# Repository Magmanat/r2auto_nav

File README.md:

# r2auto_nav
ROS2 auto_nav code for EG2310, sem2 AY21/22

Welcome to group4's repo for EG2310, and this is all our code for our Beta Gasoline robot.

Please follow our step by step guide to start up your system. We are assuming that you are using the exact same hardware as us, such as our launcher and loading system, and our electrical connections.

## Preparation
#### Do the following things to setup your laptop and turtlebot

 1. Follow the instructions here to setup your laptop and turtlebot https://emanual.robotis.com/docs/en/platform/turtlebot3/quick-start/
 2. Follow this for instructions on setting up i2c communication on the turtlebot's raspberry pi https://ask.wingware.com/question/3/i2c-problem-with-remote-raspberry-pi/
 3. Follow this for instructions on setting up gpiozero and pigpio pin factory (so that the servo used will not spasm) https://gpiozero.readthedocs.io/en/stable/remote_gpio.html
  4. Check our our /Hardware folder for the schematics of the pcbs that we use to replicate our robot system. **IMPORTANT! FOR OUR 12V SUPPLY AS STATED IN OUR RPI HAT PCB, WE USED 5V INSTEAD DUE TO 12V SPINNING OUR MOTORS TOO FAST AND CAUSING OSCILLATIONS ON OUR ROBOT**

## File allocation and building of workspaces
clone our repository into your Home directory.

    git clone https://github.com/Magmanat/r2auto_nav.git
 Then shift the entire folder hardware_bringup into your turtlebot3_ws using scp, then build the workspace, for example

    scp -r path_to_r2auto_nav/turtlebot3_ws/src/hardware_bringup ubuntu@(ip-address-of-pi):~/turtlebot3/src
    ssh ubuntu@(ip-address-of-pi)
    cd turtlebot3_ws
    colcon build
  
  cd into colcon_ws and colcon build the workspace to setup the ros package on your laptop

    cd path_to_r2auto_nav/colcon_ws
    colcon build
  Your should be done setting up after this, now its time to have fun with our package
  
  ## System check
Firstly, we will use the factory_test package to ensure that everything is running properly, we will ssh into the turtlebot and startup all the hardware publishers and subscribers.

#### For your Turtlebot
##### In one terminal
    ssh ubuntu@(ip-address-of-pi)
    roslaunch turtlebot3_bringup turtlebot3_robot.launch
##### In another terminal
    ssh ubuntu@(ip-address-of-pi)
    ros2 launch hardware_bringup hardware.launch.py
  
Finally, we will run the script in your laptop to check that the whole system is working
#### For your Laptop
##### In one terminal
    ros2 run auto_nav factory_test

Follow the instructions printed on your terminal, and if everything works out fine, it means the system is ready to go.

## Running auto_nav in a maze
Now we will get to try the robot in an actual maze, and see it complete its mission, prepare two terminals for your Turtlebot and prepare 3 terminals for your Laptop.
Similarly, we will start all the hardware in the Turtlebot first.
#### For your Turtlebot
##### In one terminal
    ssh ubuntu@(ip-address-of-pi)
    roslaunch turtlebot3_bringup turtlebot3_robot.launch
##### In another terminal
    ssh ubuntu@(ip-address-of-pi)
    ros2 launch hardware_bringup hardware.launch.py
  
Finally, we will run the commands to start the auto navigation
#### For your Laptop
##### First terminal
    ros2 launch turtlebot3_cartographer cartographer.launch.py
Ensure that you see rviz open up, laserscan and map data will be able to be seen on the rviz window.
##### Second terminal
    ros2 run auto_nav map2base
Ensure that the transforms are properly being published by observing the terminal for any error messages that print.
##### Third terminal
    ros2 run auto_nav wall_follow
Finally, after running this command, the robot should move around and perform its mission autonomously, moving around the maze and stopping at an nfc loading bay, which it will then stop and wait to be loaded and button to be pressed to continue with its mission. After moving one entire round around the maze, and also being loaded, it will then search for a thermal target, which when found, the turtlebot would start centering towards the target and finally when the target is approximately 15 cm away from the turtlebot, it would stop and start the firing sequence.

## Parameters that affect operation of the robot
From lines 35 to 57 of /colcon_ws/src/auto_nav/auto_nav/r2_wall_follow.py

The explanation of all the parameters are as commented below. These are the values which we found work the best for us in our use case. Please change these values if you require a different behavior of the robot.

    #variables affecting targeting
    TARGETspeedchange = 0.05 #forward speed for targeting
    TARGETrotatechange = 0.1 #rotation speed for targeting
    TARGET_hotthreshhold = 31 #target temperature
    TARGETshoot_distance = 0.45 #distance from center of lidar to front before shooting
    TARGET_front_angle = 3 #angle of front to measure distance
    TARGET_moveres = 0.2 #time for sleep when moving
    TARGET_target_not_detected_threshhold = 2 #How long in seconds before target considered as not detected

    # variables affecting navigation
    fastspeedchange = 0.2 #speed when bot moving fast linear speed
    slowspeedchange = 0.12 #speed when bot moving slow linear speed
    
    turning_speed_wf_fast = 1.1 #fast turning speed for bot
    turning_speed_wf_medium = 0.75 #medium turning speed for bot
    turning_speed_wf_slow = 0.5 #slow turning speed for bot
    
    front_d = 0.45 #threshhold front distance that robot should not enter
    side_d = 0.45 #threshold side distance that robot should not enter
    
    target_count_threshhold = 5 # (how long you want hot_target to be spotted before activating firing) / hot_timer_delay = target_count_threshhold
    hot_timer_delay = 0.1 # in seconds

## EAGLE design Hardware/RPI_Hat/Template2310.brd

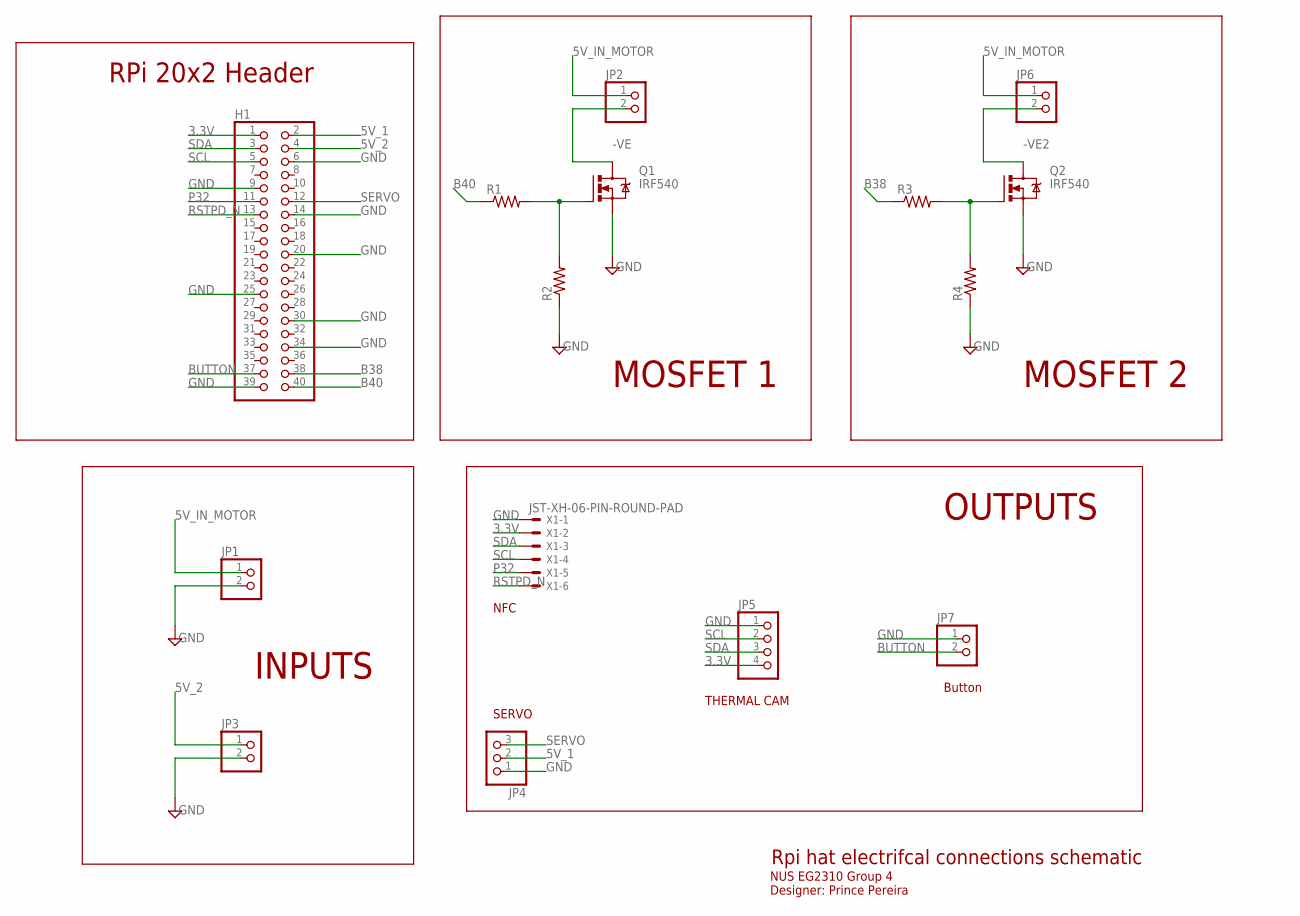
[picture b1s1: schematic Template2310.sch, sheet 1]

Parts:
H1: PINHD-2X20; 2X20
JP1, JP2, JP3, JP6: PINHD-1X2; 1X02
JP4: PINHD-1X3/90; 1X03/90
JP5: PINHD-1X4/90; 1X04/90
JP7: PINHD-1X2/90; 1X02/90
Q1, Q2: IRF540; TO220BV
R1, R2, R3, R4: R-US_0204/7; 0204/7
X1: JST-XH-06-PIN-ROUND-PAD; JST-XH-06-PACKAGE-ROUND-PAD

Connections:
3.3V: H1.1, JP5.4, X1.2
5V_1: H1.2, JP4.2
5V_2: H1.4, JP3.1
5V_IN_MOTOR: JP1.1, JP2.1, JP6.1
-VE: JP2.2, Q1.D
-VE2: JP6.2, Q2.D
B38: H1.38, R3.1
B40: H1.40, R1.1
BUTTON: H1.37, JP7.2
GND: H1.6, H1.9, H1.14, H1.20, H1.25, H1.30, H1.34, H1.39, JP1.2, JP3.2, JP4.1, JP5.1, JP7.1, Q1.S, Q2.S, R2.1, R4.1, X1.1
JUNCTION: Q1.G, R1.2, R2.2
JUNCTION1: Q2.G, R3.2, R4.2
P32: H1.11, X1.5
RSTPD_N: H1.13, X1.6
SCL: H1.5, JP5.2, X1.4
SDA: H1.3, JP5.3, X1.3
SERVO: H1.12, JP4.3

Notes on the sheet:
Rpi hat electrifcal connections schematic
NUS EG2310 Group 4 Designer: Prince Pereira
RPi 20x2 Header
MOSFET 1
INPUTS
OUTPUTS
NFC
SERVO
THERMAL CAM
MOSFET 2
Button

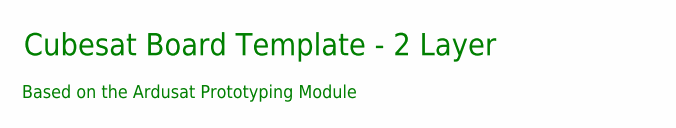
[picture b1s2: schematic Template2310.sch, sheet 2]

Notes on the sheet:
Cubesat Board Template - 2 Layer
Based on the Ardusat Prototyping Module

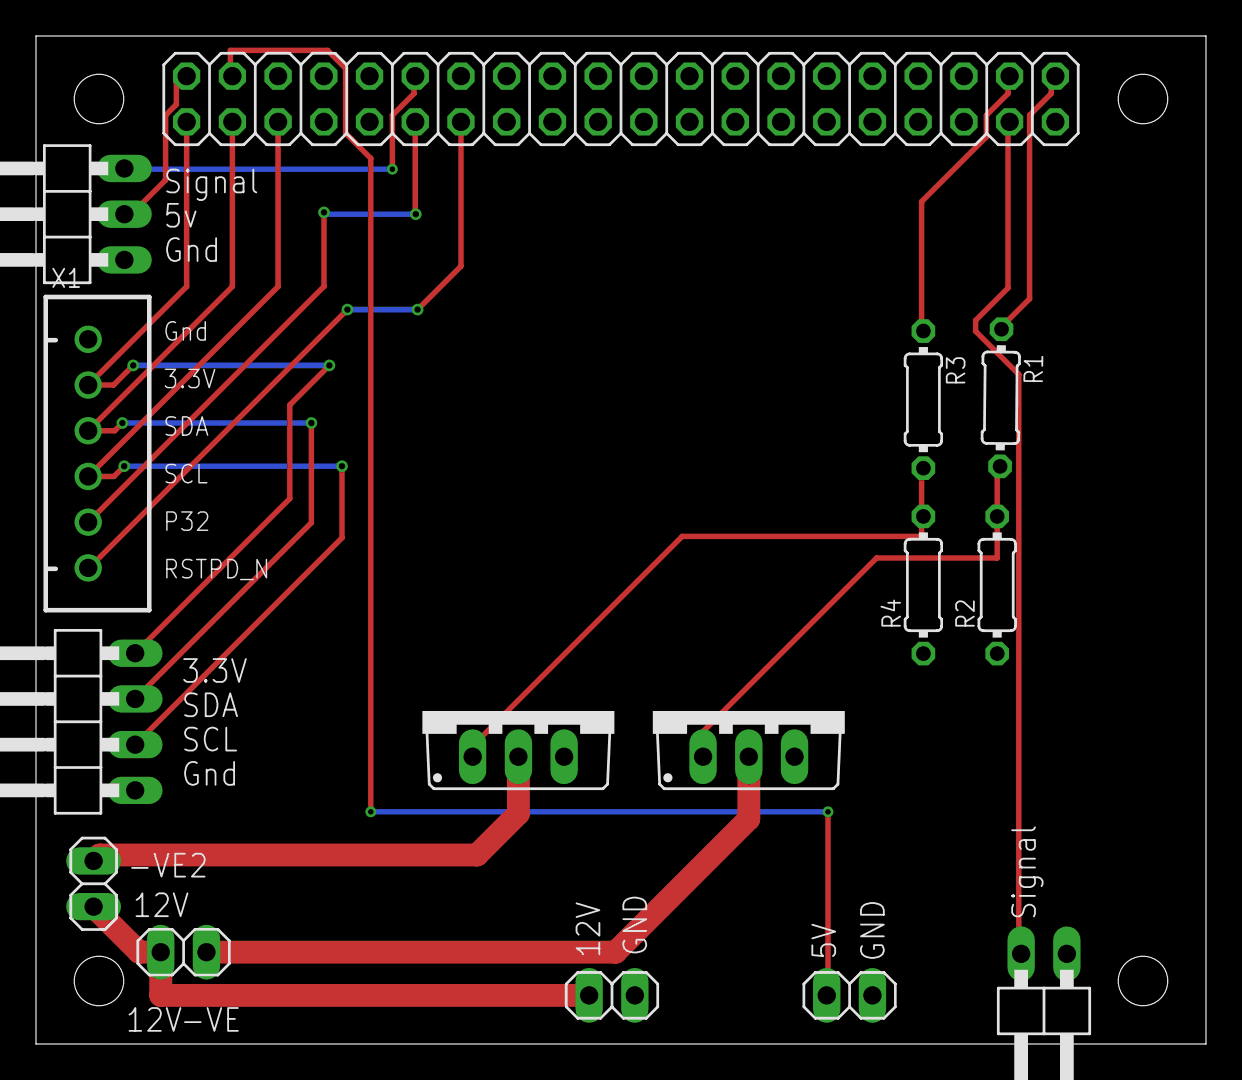
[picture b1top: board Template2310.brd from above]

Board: 2 copper layers, 65.0 x 56.0 mm, 15 parts (0 on the bottom side), 17 nets.

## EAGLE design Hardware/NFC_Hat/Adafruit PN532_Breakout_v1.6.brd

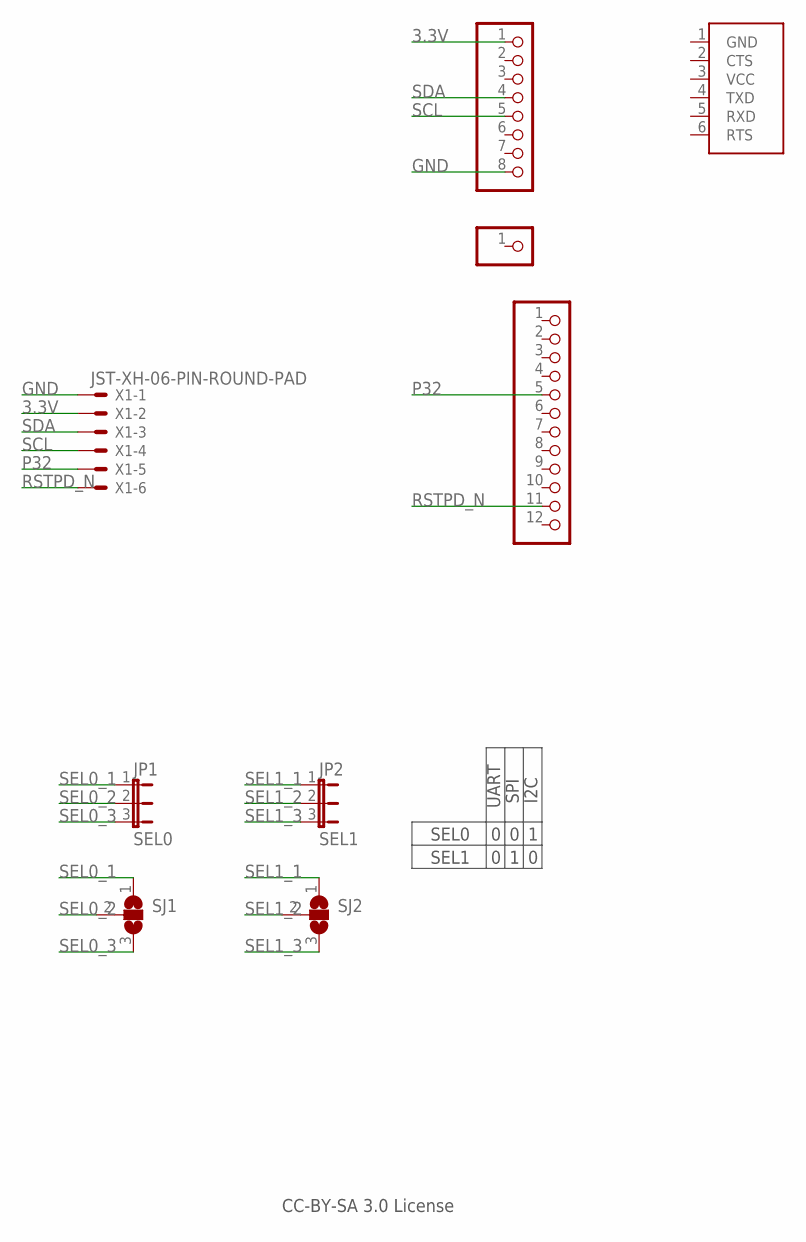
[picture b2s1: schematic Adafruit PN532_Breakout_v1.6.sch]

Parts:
CN1: FTDI; 1X06_ROUND
JP1: SEL0; JUMPER3
JP2: SEL1; JUMPER3
JP3: HEADER-1X12; 1X12_ROUND
JP4: HEADER-1X8ROUND; 1X08_ROUND
JP5: HEADER-1X1ROUND; 1X01_ROUND
SJ1, SJ2: SJ2W; SJ_2
X1: JST-XH-06-PIN-ROUND-PAD; JST-XH-06-PACKAGE-ROUND-PAD

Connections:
3.3V: JP4.1, X1.2
GND: JP4.8, X1.1
P32: JP3.5, X1.5
RSTPD_N: JP3.11, X1.6
SCL: JP4.5, X1.4
SDA: JP4.4, X1.3
SEL0_1: JP1.1, SJ1.1
SEL0_2: JP1.2, SJ1.2
SEL0_3: JP1.3, SJ1.3
SEL1_1: JP2.1, SJ2.1
SEL1_2: JP2.2, SJ2.2
SEL1_3: JP2.3, SJ2.3

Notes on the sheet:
SEL0
SEL1
UART
SPI
I2C
CC-BY-SA 3.0 License

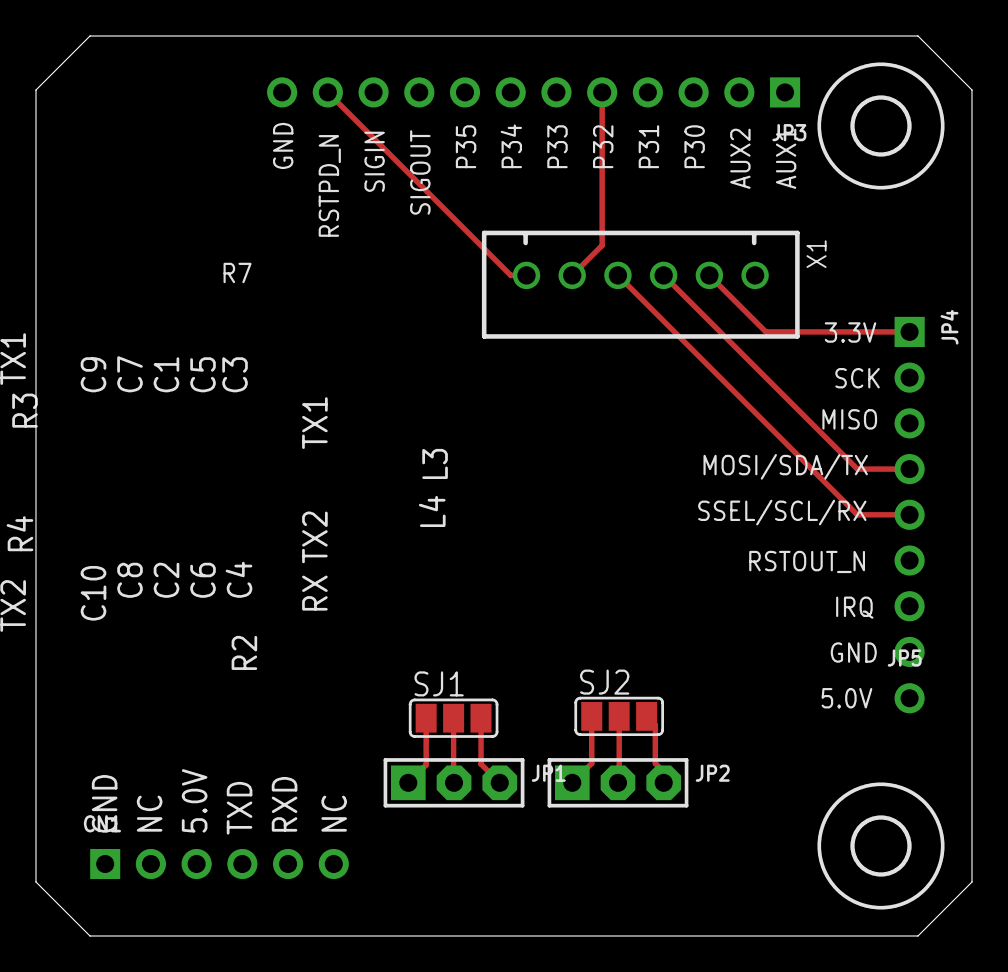
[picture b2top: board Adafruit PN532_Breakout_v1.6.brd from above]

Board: 2 copper layers, 52.0 x 50.0 mm, 11 parts (0 on the bottom side), 12 nets.

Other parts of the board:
U$37, U$38: MOUNTINGHOLE_3.0

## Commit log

2022-01-19 added users.txt and added in Prince name
2022-01-19 added github userid to users.txt
2022-01-19 Added Jeric UserID
2022-01-19 Added Username
2022-01-19 Removed Jeric's Username
2022-01-19 Update users.txt removed Jeric's username
2022-01-19 Update users.txt ADded jeric's Username
2022-01-19 Modified 'Brendan'
2022-01-19 added 'wern'
2022-01-19 add username
2022-02-10 added recursive maze and iterative maze
2022-02-11 did a minor change
2022-02-15 before changing directions
2022-02-15 made a real file and gazebo file (direction different)
2022-02-15 somehow fixed the transform error by using another node, AMAZING, but the algorithm right now is still pretty shit, but this improvement might go a long way in coding other algorithms
2022-02-20 commiting some changes
2022-02-20 Skeleton for targeting algo
2022-02-21 addded Centering and appraoch todo: 1. implement front_distance calculation 2. implement shotting sequence 3. actually test it 4. create script for interfacing and publishing thermal array
2022-02-24 files add thermal_listener -> plot updating 8x8 graph of thermal cam array thermal_publisher -> script for rpi to interface with thermal cam and publish array
    files updates
    r2targeting1 -> minor tweaks
    To-do
    1. Implement front distance
    2. implement shooting sequence
    3. Test centering
2022-02-24 trying new navigation type of algorithm
2022-02-24 bro i want to die
    updated amd added interpolation
2022-03-01 Implemented print statements and tested without bot changed to step based movement
    to do
    implment front distance (lidar)
    implement firing sequence
    implement publisher for target detected (bool)
    test with bot
2022-03-05 added front range to targeter script
2022-03-05 followed auto_nav version of checking for certain distance
2022-03-05 left wall following works
2022-03-05 added full round wall following and cutthrough algo
2022-03-10 changed some wall follow
2022-03-10 changed targeting.py
2022-03-10 implement r2_targeting into wall follow
2022-03-10 BOOM, Wall following + NFC + Button + Thermal in one run
2022-03-15 changed some stuff
2022-03-15 some changes
2022-03-22 added turtlebot ws as a backup
2022-03-22 changed distances to angles
2022-04-02 deleted useless code, tried to add all variables that can change at top of script, commented some code, made the bot rotate if target detected but suddenly missing, somewhat improved the wall followi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
2022-04-05 good code, everything works except no right wall following
2022-04-07 trial test successful on full batt
2022-04-07 final test?
2022-04-08 added redundancy for loss lidar data and also added factory acceptance test
2022-04-10 final code for final run
2022-04-13 colcon_ws + turtlebot3_ws
2022-04-13 small change
2022-04-13 some changes to working tree
2022-04-13 added turtlebot stuff to src
2022-04-13 added comments to the repo
2022-04-13 removed build and install
2022-04-13 Create README.md
    added README.md
2022-04-18 removed counters for firing node
2022-04-21 added pcb schematics
